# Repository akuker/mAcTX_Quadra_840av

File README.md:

# mAcTX_Quadra_840av
Adapter board to allow an ATX Power Supply to be used with a Quadra 840av

Mouser Bill of Materials: https://www.mouser.com/ProjectManager/ProjectDetail.aspx?AccessID=3659aac31a

Schematic: [mAcTX_Quadra_840av.pdf](mAcTX_Quadra_840av/mAcTX_Quadra_840av_sch.pdf)

Note: I used a 2N3904 NPN transistor for the soft power circuit. Others may work as well.

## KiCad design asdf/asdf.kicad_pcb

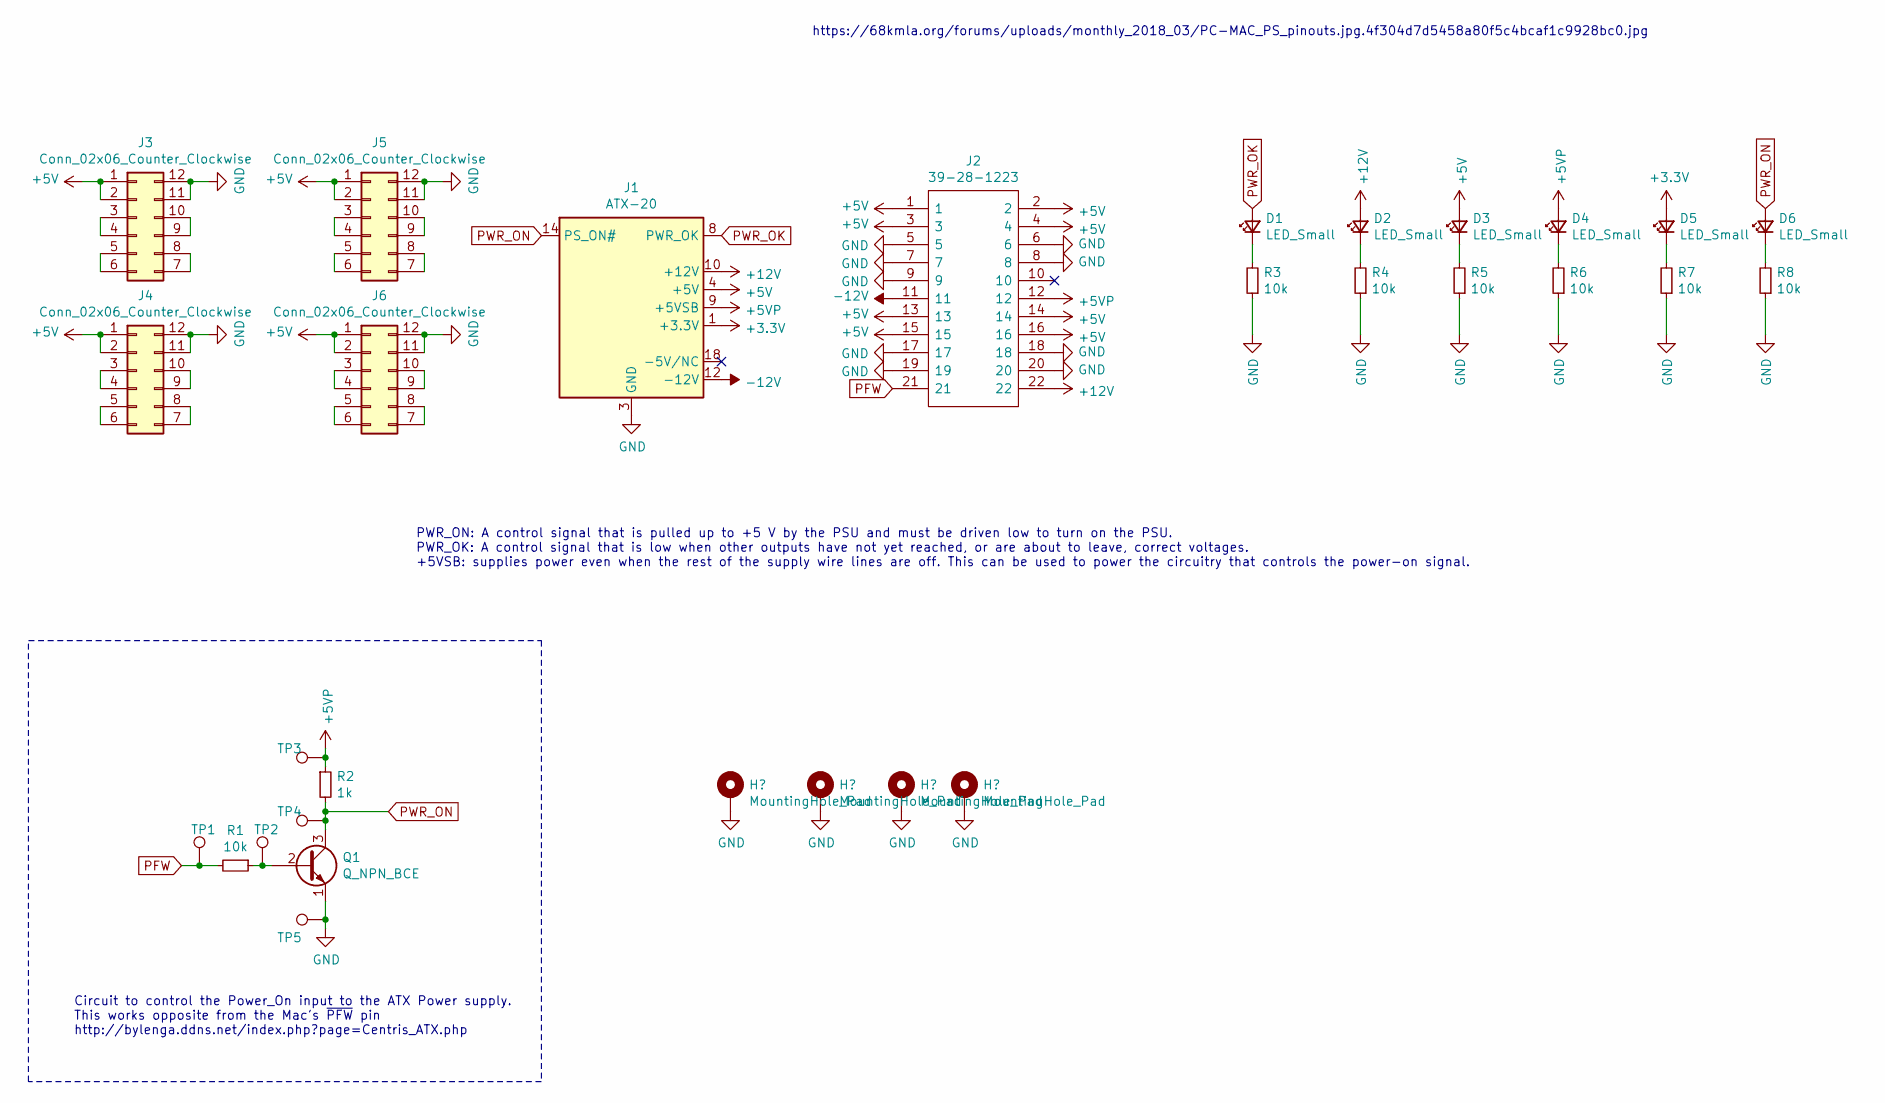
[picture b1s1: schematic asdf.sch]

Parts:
D1, D2, D3, D4, D5, D6: LED_Small; LED_D3.0mm
J1: ATX-20; Molex_Mini-Fit_Jr_5566-20A_2x10_P4.20mm_Vertical
J2: 39-28-1223; SHDR22W125P420_2X11_4740X960X1310P; Mouser Part Number 538-39-28-1223
J3, J4, J5, J6: Conn_02x06_Counter_Clockwise; PinHeader_2x06_P2.54mm_Vertical
Q1: Q_NPN_BCE; TO-92
R1, R3, R4, R5, R6, R7, R8: 10k; R_Axial_DIN0204_L3.6mm_D1.6mm_P7.62mm_Horizontal
R2: 1k; R_Axial_DIN0204_L3.6mm_D1.6mm_P7.62mm_Horizontal
TP1, TP2, TP3, TP4, TP5: TestPoint; TestPoint_THTPad_D1.0mm_Drill0.5mm

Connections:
+3V3: D5.2 (A), J1.1 (+3.3V), J1.2 (+3.3V), J1.11 (+3.3V)
+5V: D3.2 (A), J1.4 (+5V), J1.6 (+5V), J1.19 (+5V), J1.20 (+5V), J2.1, J2.2, J2.3, J2.4, J2.13, J2.14, J2.15, J2.16, J3.1, J3.2, J4.1, J4.2, J5.1, J5.2, J6.1, J6.2
+5VP: D4.2 (A), J1.9 (+5VSB), J2.12, R2.1, TP3.1
+12V: D2.2 (A), J1.10 (+12V), J2.22
-12V: J1.12 (-12V), J2.11
GND: J1.3 (GND), J1.5 (GND), J1.7 (GND), J1.13 (GND), J1.15 (GND), J1.16 (GND), J1.17 (GND), J2.5, J2.6, J2.7, J2.8, J2.9, J2.17, J2.18, J2.19, J2.20, J3.11, J3.12, J4.11, J4.12, J5.11, J5.12, J6.11, J6.12, Q1.1 (E), R3.1, R4.1, R5.1, R6.1, R7.1, R8.1, TP5.1; also elsewhere on the board
unnamed: D1.1 (K), R3.2
unnamed: D2.1 (K), R4.2
unnamed: D3.1 (K), R5.2
unnamed: D4.1 (K), R6.2
unnamed: D5.1 (K), R7.2
unnamed: D6.1 (K), R8.2
unnamed: J3.3, J3.4
unnamed: J3.5, J3.6
unnamed: J3.7, J3.8
unnamed: J3.9, J3.10
unnamed: J4.3, J4.4
unnamed: J4.5, J4.6
unnamed: J4.7, J4.8
unnamed: J4.9, J4.10
unnamed: J5.3, J5.4
unnamed: J5.5, J5.6
unnamed: J5.7, J5.8
unnamed: J5.9, J5.10
unnamed: J6.3, J6.4
unnamed: J6.5, J6.6
unnamed: J6.7, J6.8
unnamed: J6.9, J6.10
unnamed: Q1.2 (B), R1.1, TP2.1
PFW: J2.21, R1.2, TP1.1
PWR_OK: D1.2 (A), J1.8 (PWR_OK)
PWR_ON: D6.2 (A), J1.14 (PS_ON#), Q1.3 (C), R2.2, TP4.1

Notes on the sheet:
https://68kmla.org/forums/uploads/monthly_2018_03/PC-MAC_PS_pinouts.jpg.4f304d7d5458a80f5c4bcaf1c9928bc0.jpg
PWR_ON: A control signal that is pulled up to +5 V by the PSU and must be driven low to turn on the PSU. PWR_OK: A control signal that is low when other outputs have not yet reached, or are about to leave, correct voltages. +5VSB: supplies power even when the rest of the supply wire lines are off. 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
Circuit to control the Power_On input to the ATX Power supply. This works opposite from the Mac's ~PFW pin http://bylenga.ddns.net/index.php?page=Centris_ATX.php

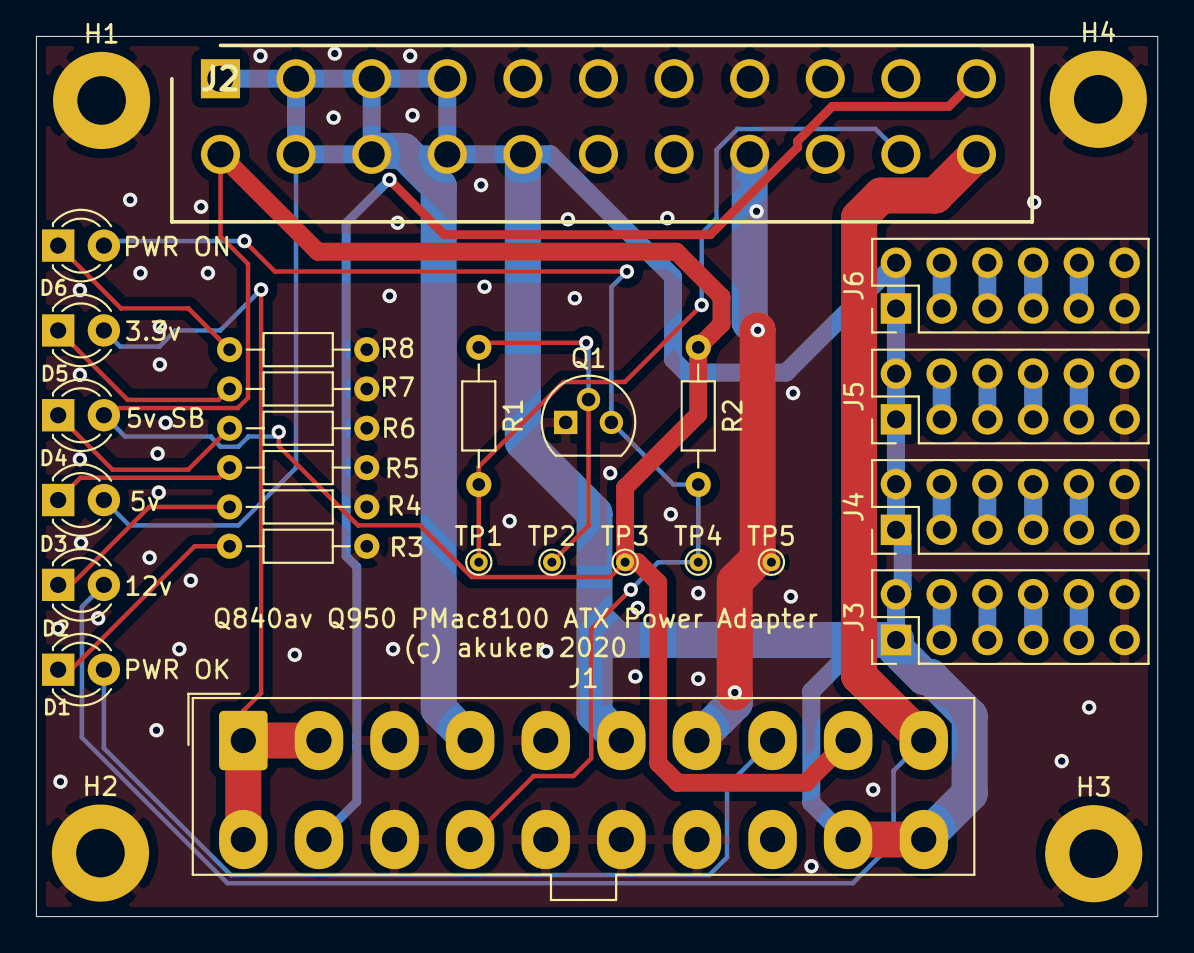
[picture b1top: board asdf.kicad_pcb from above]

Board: 2 copper layers, 62.3 x 48.9 mm, 30 parts (0 on the bottom side), 32 nets.

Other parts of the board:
H1, H2, H3, H4: MountingHole_Pad; MountingHole_2.7mm_M2.5_Pad

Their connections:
GND: H1.1, H2.1, H3.1, H4.1; also elsewhere on the board

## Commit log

2020-09-17 Initial draft
    Initial draft of a ATX -> Quadra 840av power supply adapter
2020-09-17 Rename file
2020-09-17 Updated for BadGoldEagle's comments
2021-05-18 Add images from 68kmla forums
2021-05-18 Update README.md
    Added pictures and links
2021-05-18 Updated schematic to show which parts should not be populated
2021-05-18 illustration of DNP parts
